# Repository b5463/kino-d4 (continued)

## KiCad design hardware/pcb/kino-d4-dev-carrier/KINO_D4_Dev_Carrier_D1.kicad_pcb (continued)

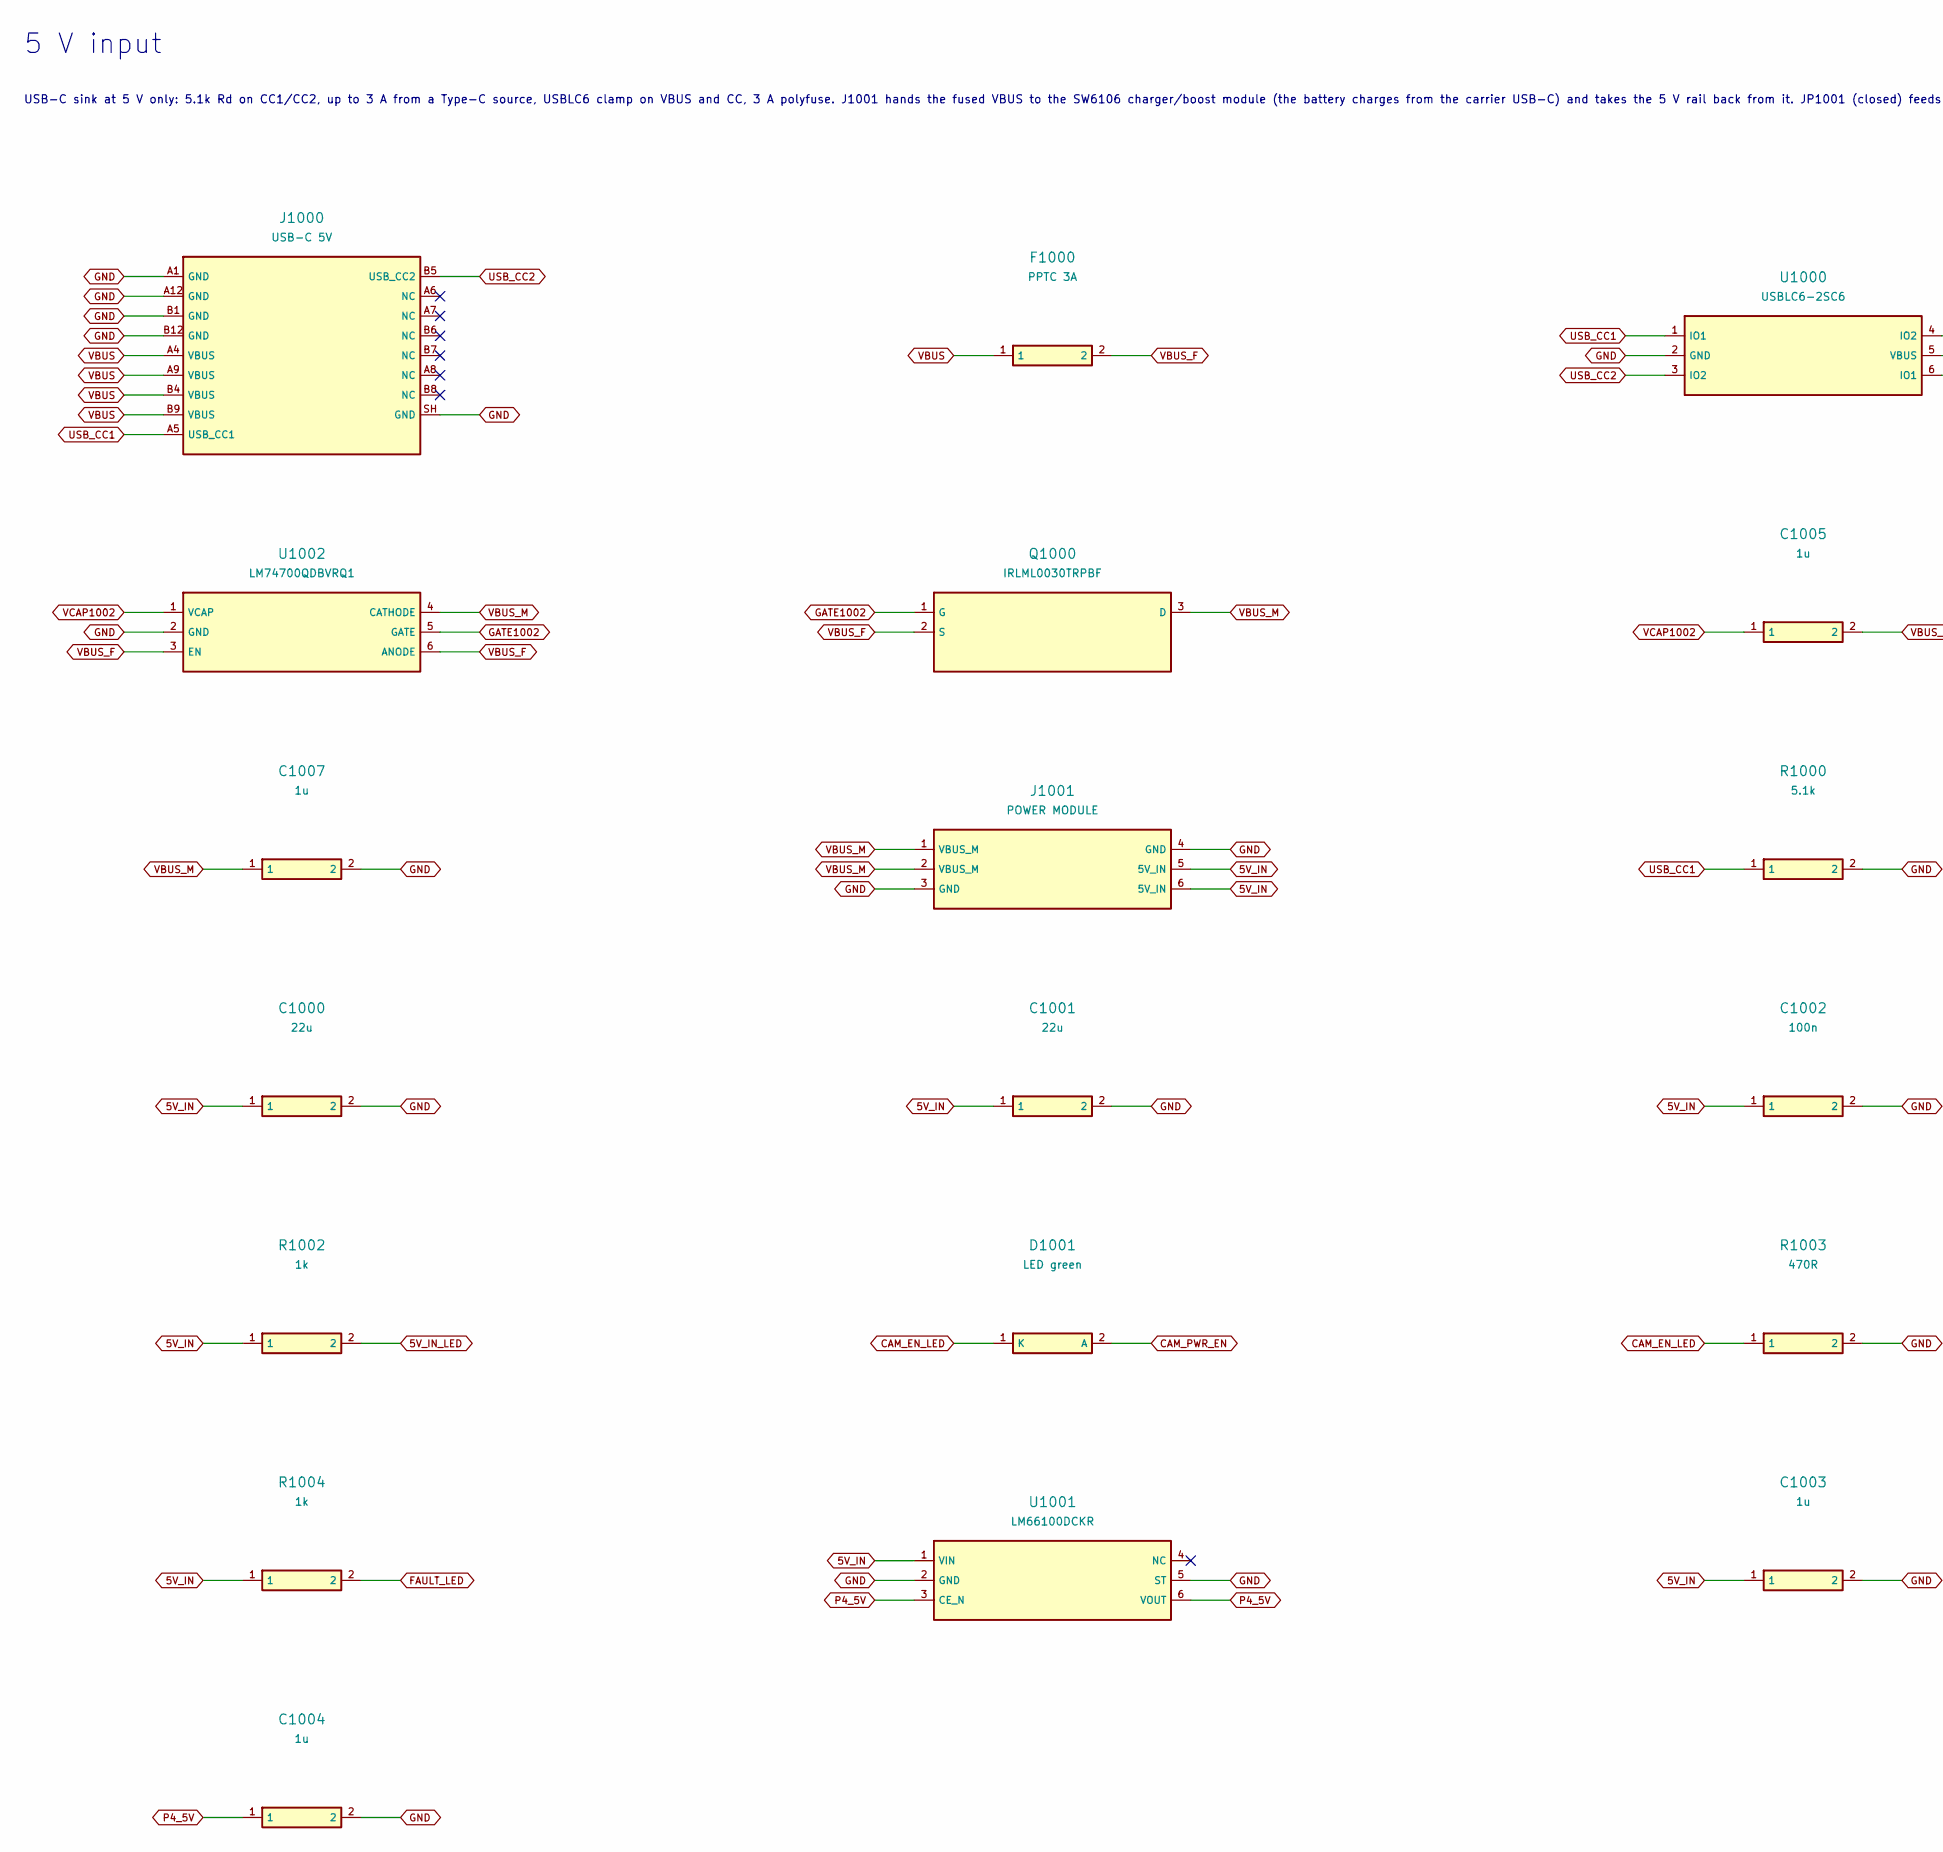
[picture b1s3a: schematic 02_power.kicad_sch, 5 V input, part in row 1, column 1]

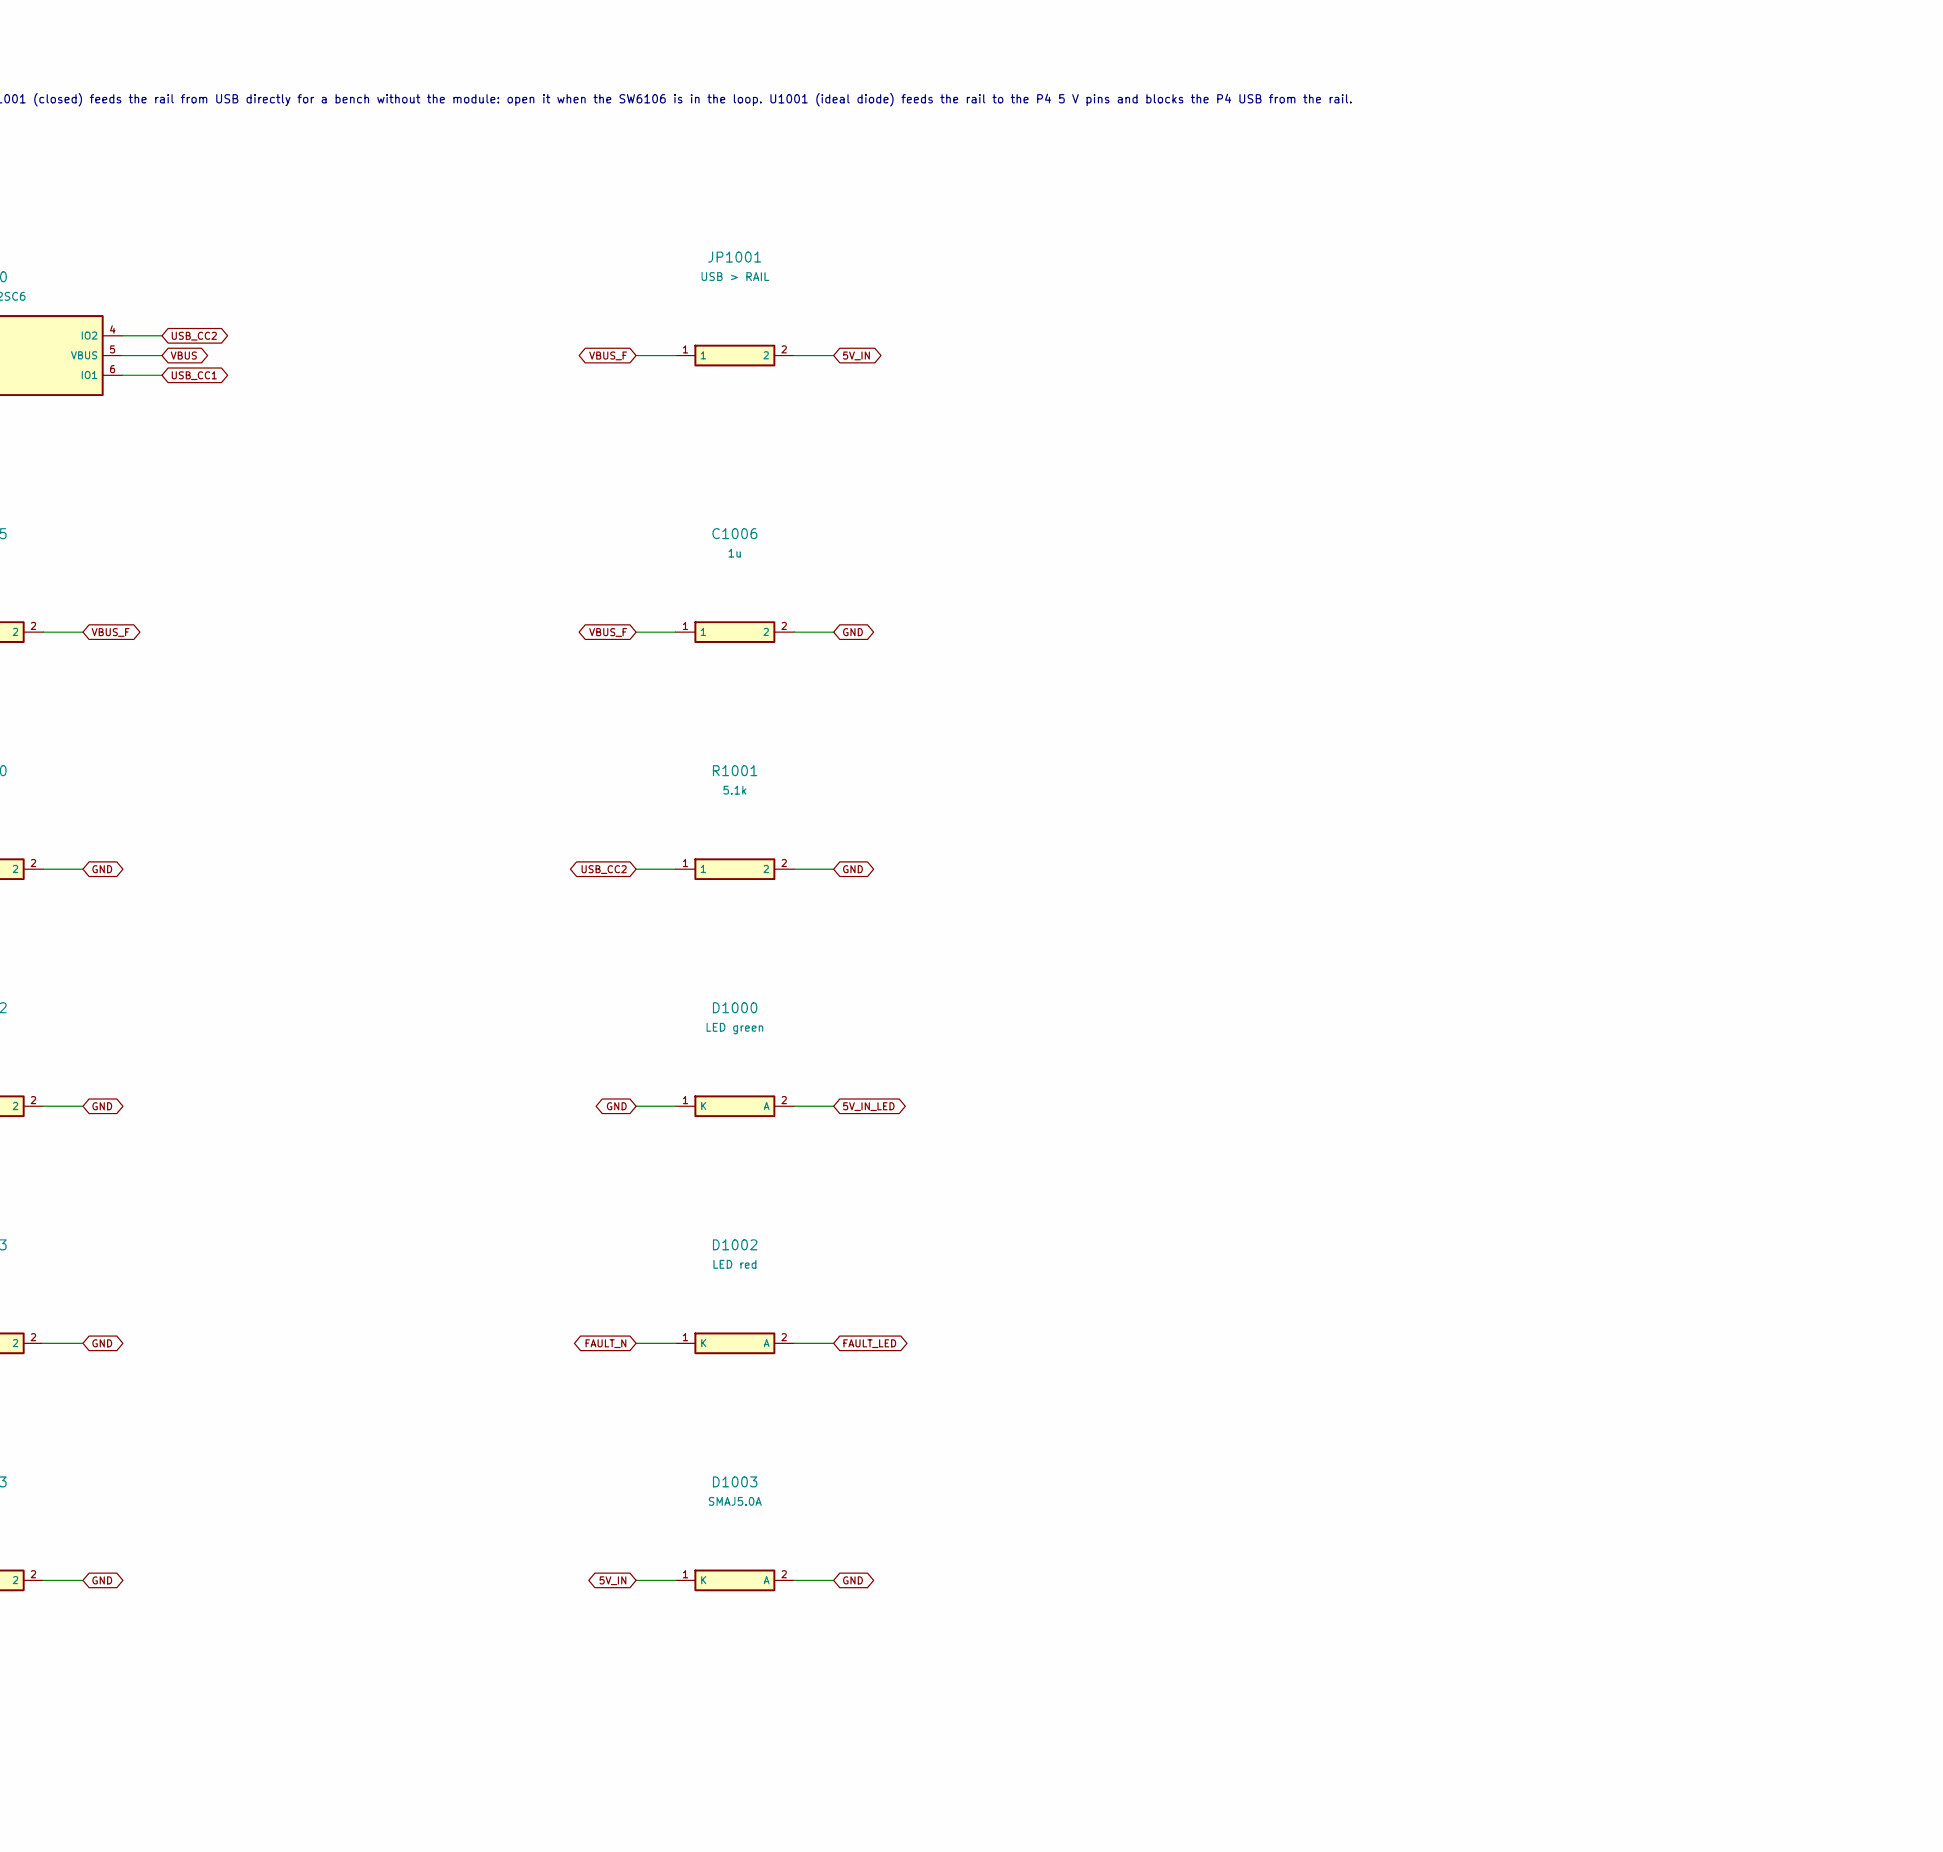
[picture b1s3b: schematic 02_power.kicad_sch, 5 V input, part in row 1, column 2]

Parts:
C1000, C1001: 22u; C_0805_2012Metric; LCSC C45783
C1002: 100n; C_0603_1608Metric; LCSC C14663
C1003, C1004, C1005, C1006, C1007: 1u; C_0603_1608Metric; LCSC C15849
D1000, D1001: LED green; LED_0805_2012Metric; LCSC C2297
D1002: LED red; LED_0603_1608Metric; LCSC C2286
D1003: SMAJ5.0A; D_SMA; LCSC C10758
F1000: PPTC 3A; Fuse_1812_4532Metric
J1000: USB-C 5V; USB_C_GCT_USB4105_KINO_GND0.05; LCSC C3020560
J1001: POWER MODULE; JST_XH_B6B-XH-A_1x06_P2.50mm_Vertical
JP1001: USB > RAIL; SolderJumper-2_P1.3mm_Bridged_RoundedPad1.0x1.5mm
Q1000: IRLML0030TRPBF; SOT-23; LCSC C67272
R1000, R1001: 5.1k; R_0603_1608Metric; LCSC C23186
R1002, R1004: 1k; R_0603_1608Metric; LCSC C21190
R1003: 470R; R_0603_1608Metric; LCSC C23179
U1000: USBLC6-2SC6; SOT-23-6; LCSC C7519
U1001: LM66100DCKR; SOT-363_SC-70-6; LCSC C2869734
U1002: LM74700QDBVRQ1; SOT-23-6; LCSC C2941042

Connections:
5V_IN: C1000.1, C1001.1, C1002.1, C1003.1, D1003.1 (K), J1001.5 (5V_IN), J1001.6 (5V_IN), JP1001.2, R1002.1, R1004.1, U1001.1 (VIN); also elsewhere on the board
5V_IN_LED: D1000.2 (A), R1002.2
CAM_EN_LED: D1001.1 (K), R1003.1
CAM_PWR_EN: D1001.2 (A); also elsewhere on the board
FAULT_LED: D1002.2 (A), R1004.2
FAULT_N: D1002.1 (K); also elsewhere on the board
GATE1002: Q1000.1 (G), U1002.5 (GATE)
GND: C1000.2, C1001.2, C1002.2, C1003.2, C1004.2, C1006.2, C1007.2, D1000.1 (K), D1003.2 (A), J1000.A1 (GND), J1000.A12 (GND), J1000.B1 (GND), J1000.B12 (GND), J1000.SH (GND), J1001.3 (GND), J1001.4 (GND), R1000.2, R1001.2, R1003.2, U1000.2 (GND), U1001.2 (GND), U1001.5 (ST), U1002.2 (GND); also elsewhere on the board
P4_5V: C1004.1, U1001.3 (CE_N), U1001.6 (VOUT); also elsewhere on the board
USB_CC1: J1000.A5 (USB_CC1), R1000.1, U1000.1 (IO1), U1000.6 (IO1)
USB_CC2: J1000.B5 (USB_CC2), R1001.1, U1000.3 (IO2), U1000.4 (IO2)
VBUS: F1000.1, J1000.A4 (VBUS), J1000.A9 (VBUS), J1000.B4 (VBUS), J1000.B9 (VBUS), U1000.5 (VBUS)
VBUS_F: C1005.2, C1006.1, F1000.2, JP1001.1, Q1000.2 (S), U1002.3 (EN), U1002.6 (ANODE)
VBUS_M: C1007.1, J1001.1 (VBUS_M), J1001.2 (VBUS_M), Q1000.3 (D), U1002.4 (CATHODE)
VCAP1002: C1005.1, U1002.1 (VCAP)

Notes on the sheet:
5 V input
USB-C sink at 5 V only: 5.1k Rd on CC1/CC2, up to 3 A from a Type-C source, USBLC6 clamp on VBUS and CC, 3 A polyfuse. J1001 hands the fused VBUS to the SW6106 charger/boost module (the battery charges from the carrier USB-C) and takes the 5 V rail back from it. JP1001 (closed) feeds the rail from 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

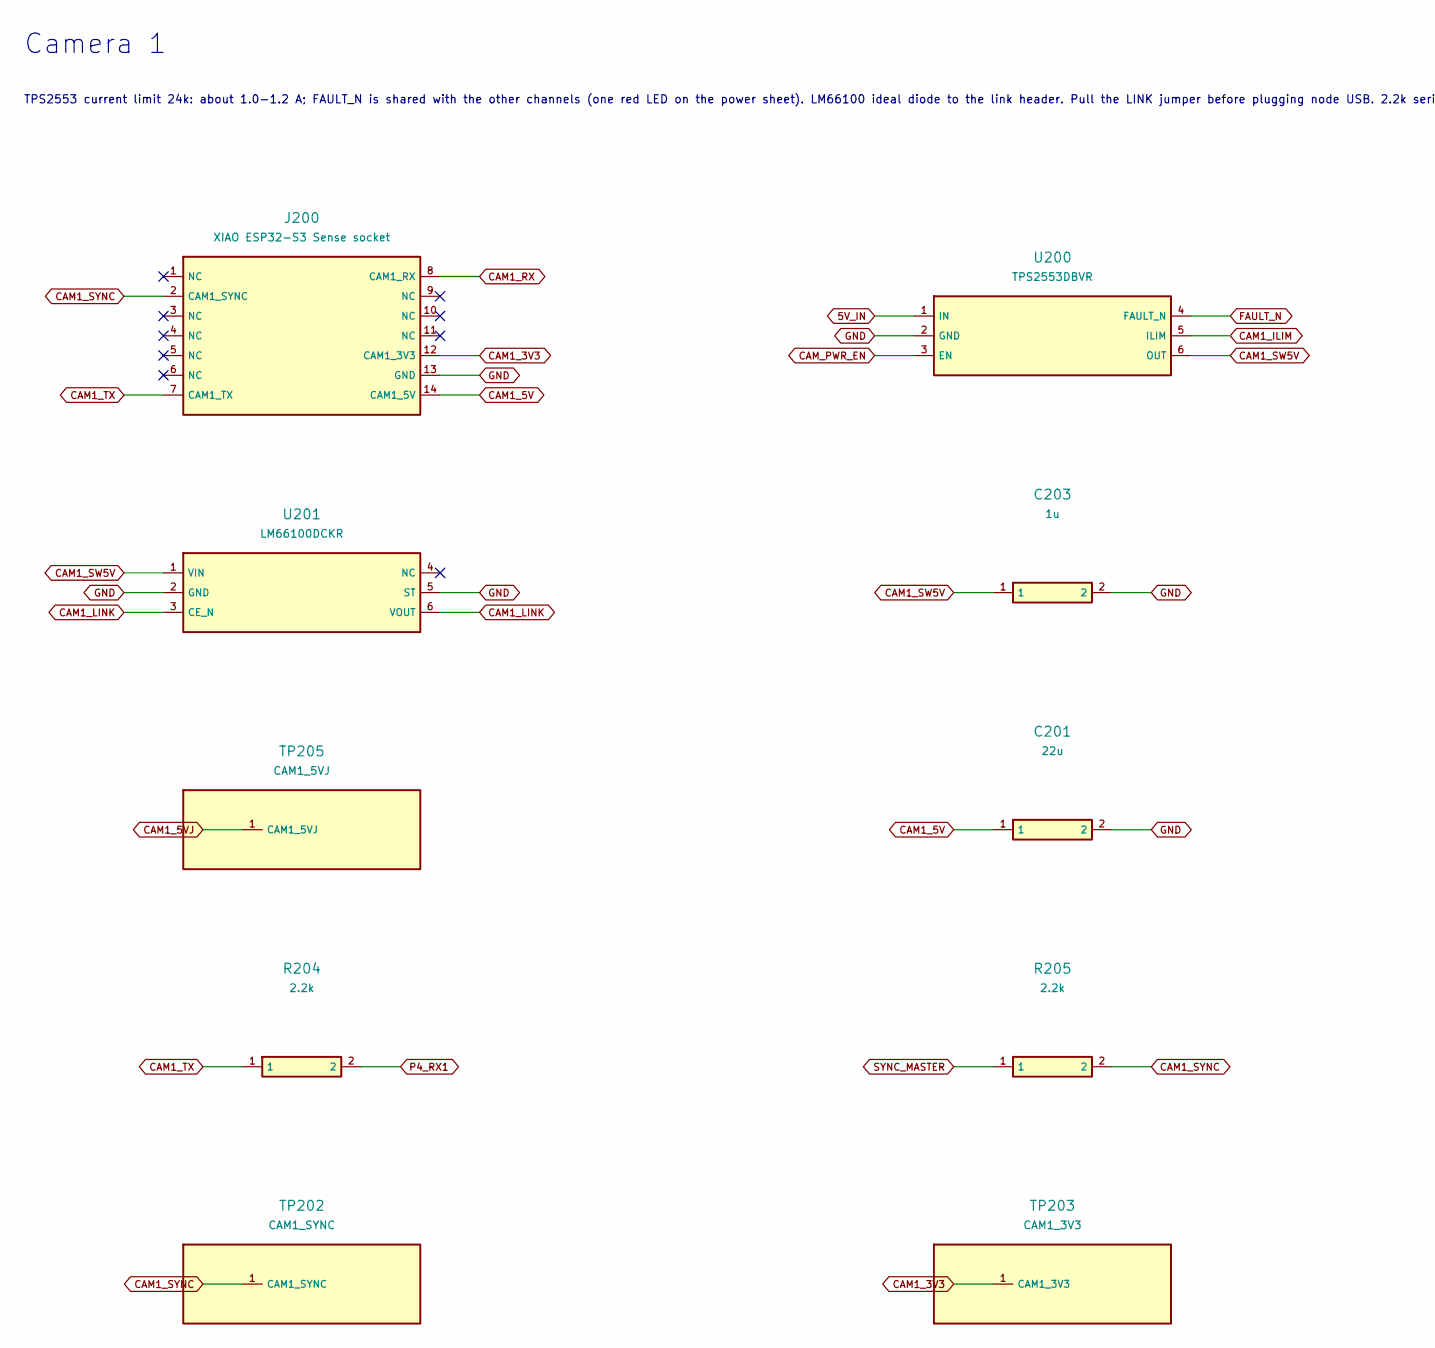
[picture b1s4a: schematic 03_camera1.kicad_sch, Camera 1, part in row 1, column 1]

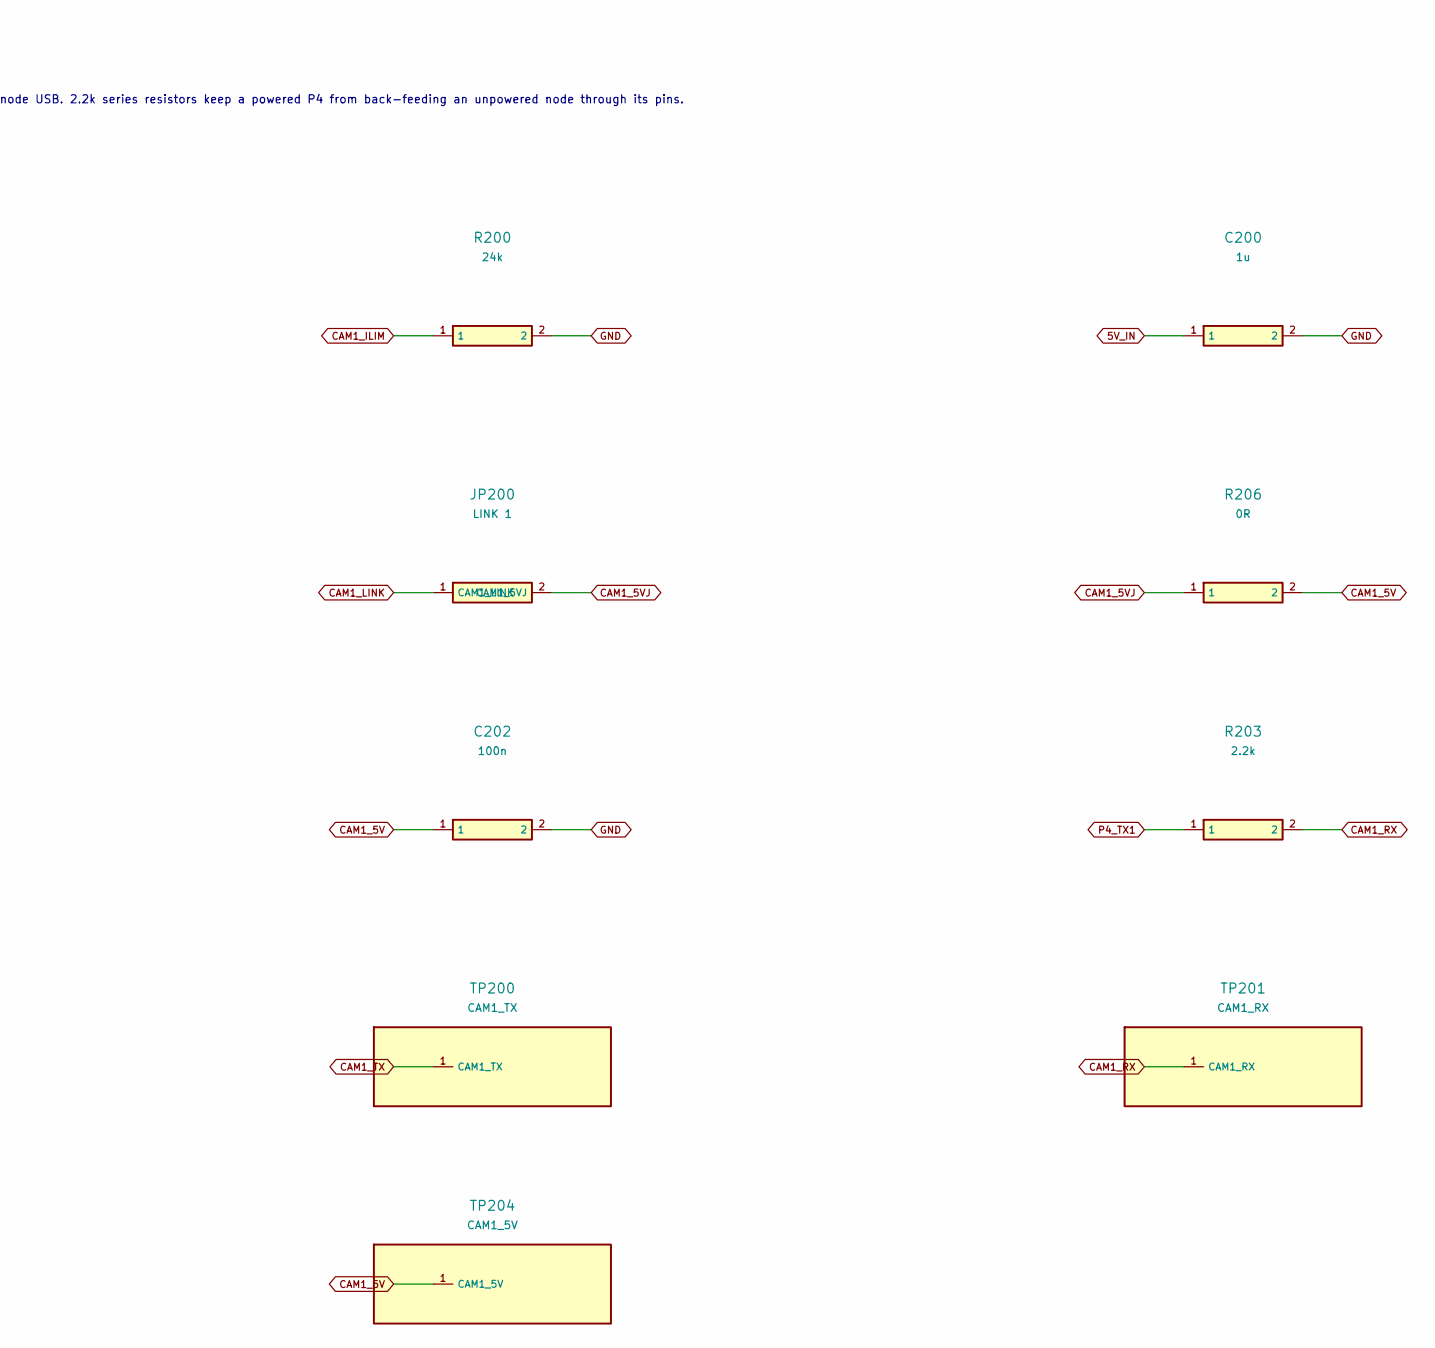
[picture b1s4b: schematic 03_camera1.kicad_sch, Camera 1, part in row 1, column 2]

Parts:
C200, C203: 1u; C_0603_1608Metric; LCSC C15849
C201: 22u; C_0805_2012Metric; LCSC C45783
C202: 100n; C_0603_1608Metric; LCSC C14663
J200: XIAO ESP32-S3 Sense socket; XIAO_Socket_15.24mm
JP200: LINK 1; PinHeader_1x02_P2.54mm_Vertical
R200: 24k; R_0603_1608Metric; LCSC C23352
R203, R204, R205: 2.2k; R_0603_1608Metric; LCSC C4190
R206: 0R; R_0603_1608Metric; LCSC C21189
TP200: CAM1_TX; TestPoint_Pad_D1.5mm
TP201: CAM1_RX; TestPoint_Pad_D1.5mm
TP202: CAM1_SYNC; TestPoint_Pad_D1.5mm
TP203: CAM1_3V3; TestPoint_Pad_D1.5mm
TP204: CAM1_5V; TestPoint_Pad_D1.5mm
TP205: CAM1_5VJ; TestPoint_Pad_D1.5mm
U200: TPS2553DBVR; SOT-23-6; LCSC C55266
U201: LM66100DCKR; SOT-363_SC-70-6; LCSC C2869734

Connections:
5V_IN: C200.1, U200.1 (IN); also elsewhere on the board
CAM1_3V3: J200.12 (CAM1_3V3), TP203.1
CAM1_5V: C201.1, C202.1, J200.14 (CAM1_5V), R206.2, TP204.1
CAM1_5VJ: JP200.2 (CAM1_5VJ), R206.1, TP205.1
CAM1_ILIM: R200.1, U200.5 (ILIM)
CAM1_LINK: JP200.1 (CAM1_LINK), U201.3 (CE_N), U201.6 (VOUT)
CAM1_RX: J200.8 (CAM1_RX), R203.2, TP201.1
CAM1_SW5V: C203.1, U200.6 (OUT), U201.1 (VIN)
CAM1_SYNC: J200.2 (CAM1_SYNC), R205.2, TP202.1
CAM1_TX: J200.7 (CAM1_TX), R204.1, TP200.1
CAM_PWR_EN: U200.3 (EN); also elsewhere on the board
FAULT_N: U200.4 (FAULT_N); also elsewhere on the board
GND: C200.2, C201.2, C202.2, C203.2, J200.13 (GND), R200.2, U200.2 (GND), U201.2 (GND), U201.5 (ST); also elsewhere on the board
P4_RX1: R204.2; also elsewhere on the board
P4_TX1: R203.1; also elsewhere on the board
SYNC_MASTER: R205.1; also elsewhere on the board

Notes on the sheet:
Camera 1
TPS2553 current limit 24k: about 1.0-1.2 A; FAULT_N is shared with the other channels (one red LED on the power sheet). LM66100 ideal diode to the link header. Pull the LINK jumper before plugging node USB. 2.2k series resistors keep a powered P4 from back-feeding an unpowered node through its pins.

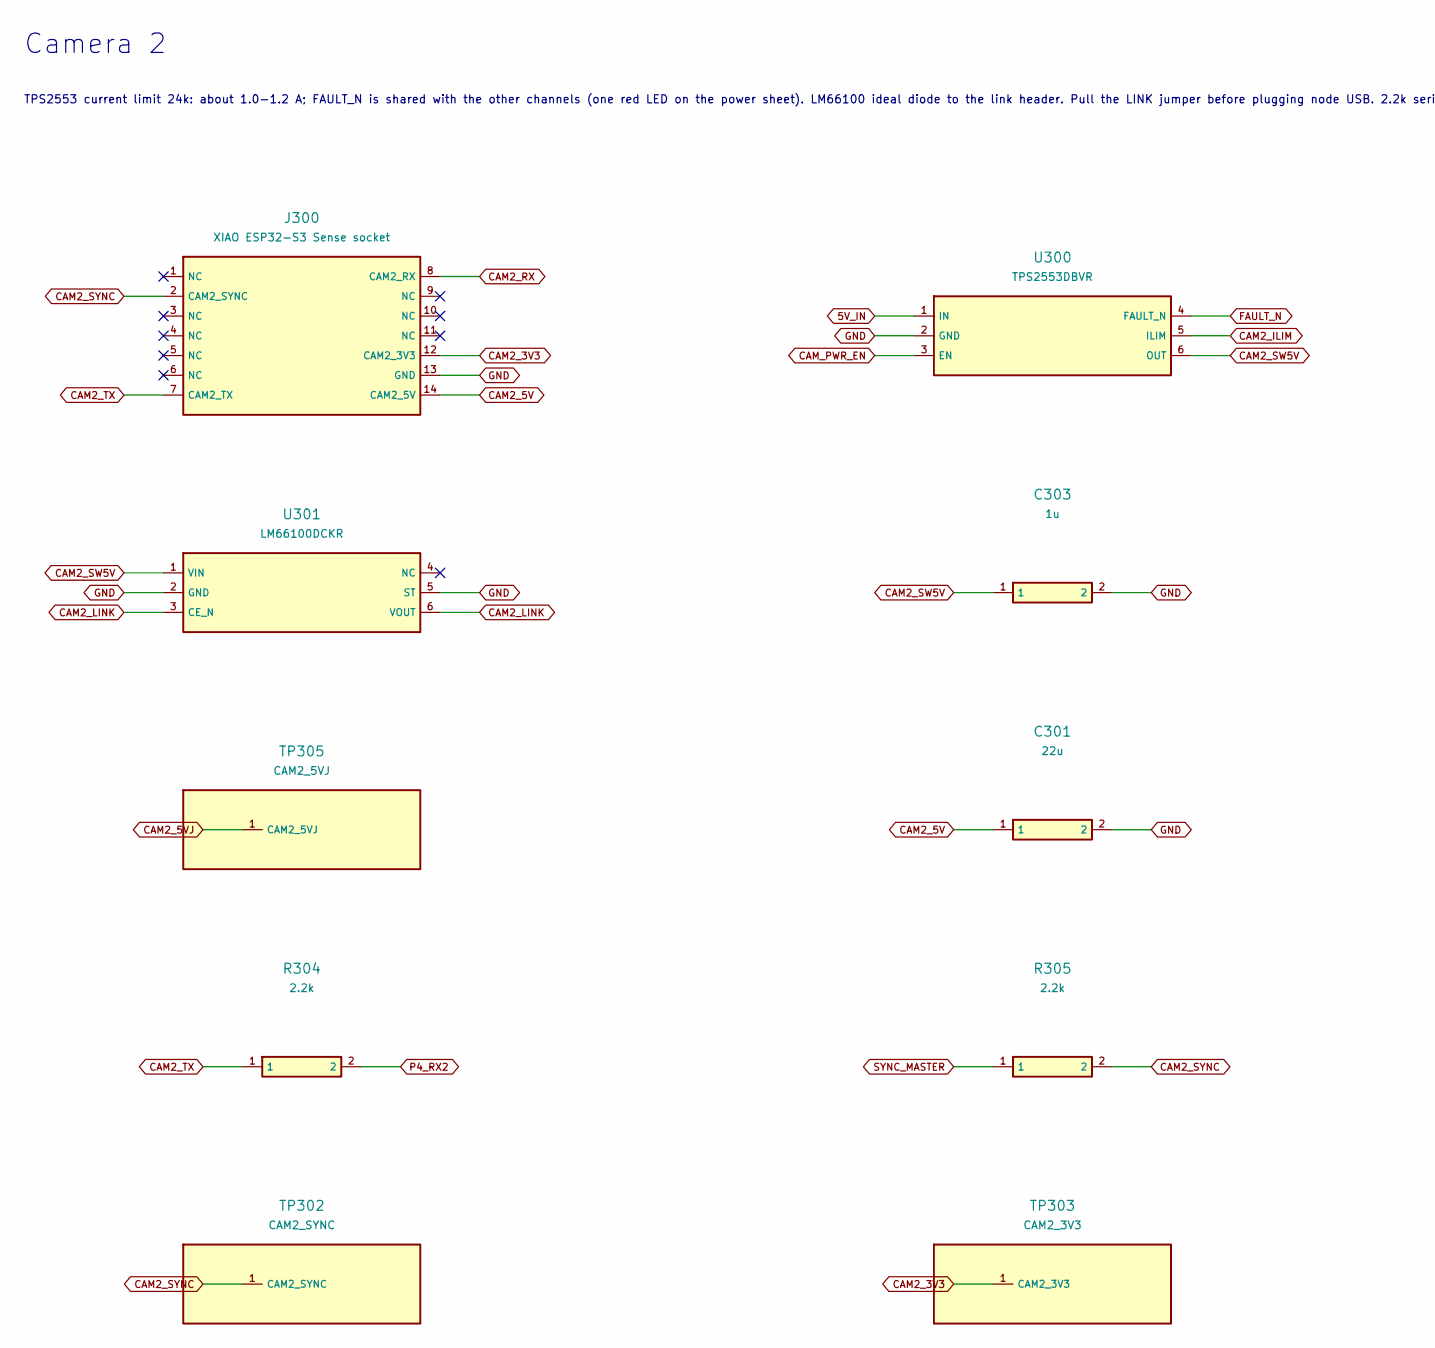
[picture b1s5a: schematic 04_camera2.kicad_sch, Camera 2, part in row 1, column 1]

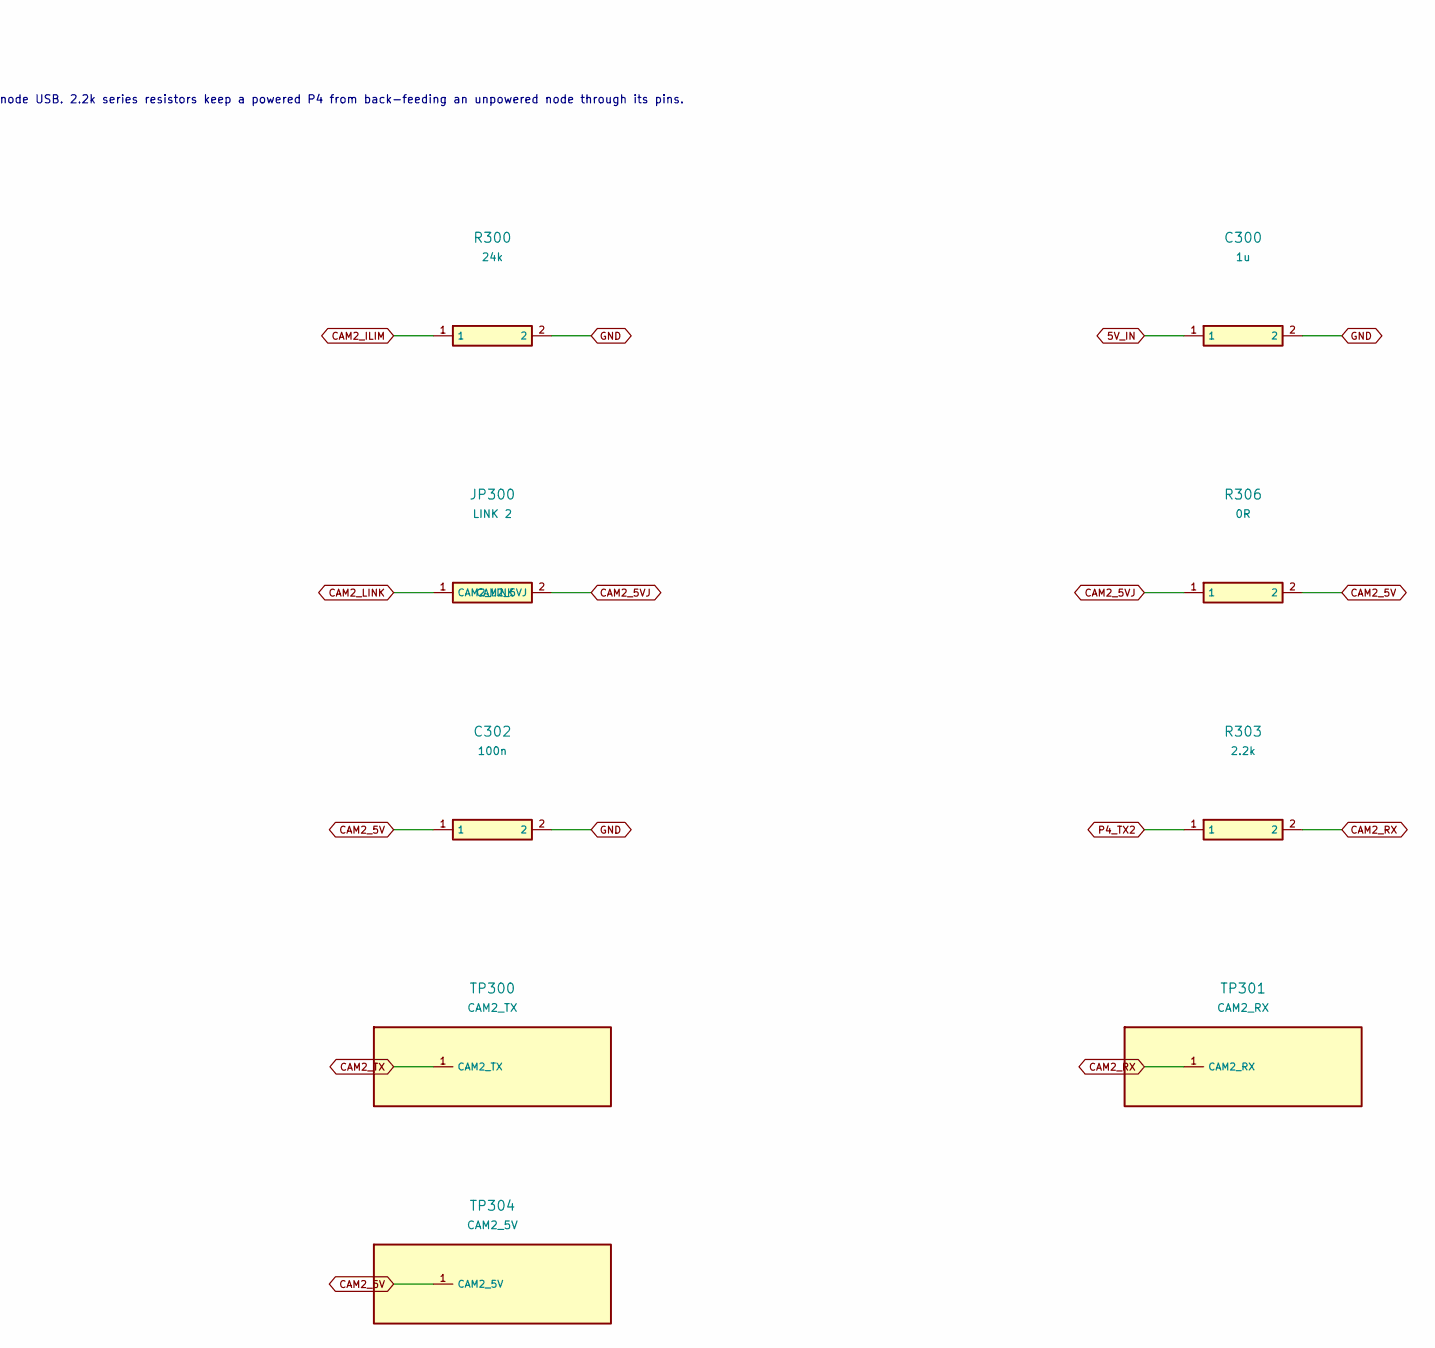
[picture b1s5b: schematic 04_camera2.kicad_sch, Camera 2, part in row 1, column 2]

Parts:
C300, C303: 1u; C_0603_1608Metric; LCSC C15849
C301: 22u; C_0805_2012Metric; LCSC C45783
C302: 100n; C_0603_1608Metric; LCSC C14663
J300: XIAO ESP32-S3 Sense socket; XIAO_Socket_15.24mm
JP300: LINK 2; PinHeader_1x02_P2.54mm_Vertical
R300: 24k; R_0603_1608Metric; LCSC C23352
R303, R304, R305: 2.2k; R_0603_1608Metric; LCSC C4190
R306: 0R; R_0603_1608Metric; LCSC C21189
TP300: CAM2_TX; TestPoint_Pad_D1.5mm
TP301: CAM2_RX; TestPoint_Pad_D1.5mm
TP302: CAM2_SYNC; TestPoint_Pad_D1.5mm
TP303: CAM2_3V3; TestPoint_Pad_D1.5mm
TP304: CAM2_5V; TestPoint_Pad_D1.5mm
TP305: CAM2_5VJ; TestPoint_Pad_D1.5mm
U300: TPS2553DBVR; SOT-23-6; LCSC C55266
U301: LM66100DCKR; SOT-363_SC-70-6; LCSC C2869734

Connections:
5V_IN: C300.1, U300.1 (IN); also elsewhere on the board
CAM2_3V3: J300.12 (CAM2_3V3), TP303.1
CAM2_5V: C301.1, C302.1, J300.14 (CAM2_5V), R306.2, TP304.1
CAM2_5VJ: JP300.2 (CAM2_5VJ), R306.1, TP305.1
CAM2_ILIM: R300.1, U300.5 (ILIM)
CAM2_LINK: JP300.1 (CAM2_LINK), U301.3 (CE_N), U301.6 (VOUT)
CAM2_RX: J300.8 (CAM2_RX), R303.2, TP301.1
CAM2_SW5V: C303.1, U300.6 (OUT), U301.1 (VIN)
CAM2_SYNC: J300.2 (CAM2_SYNC), R305.2, TP302.1
CAM2_TX: J300.7 (CAM2_TX), R304.1, TP300.1
CAM_PWR_EN: U300.3 (EN); also elsewhere on the board
FAULT_N: U300.4 (FAULT_N); also elsewhere on the board
GND: C300.2, C301.2, C302.2, C303.2, J300.13 (GND), R300.2, U300.2 (GND), U301.2 (GND), U301.5 (ST); also elsewhere on the board
P4_RX2: R304.2; also elsewhere on the board
P4_TX2: R303.1; also elsewhere on the board
SYNC_MASTER: R305.1; also elsewhere on the board

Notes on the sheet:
Camera 2
TPS2553 current limit 24k: about 1.0-1.2 A; FAULT_N is shared with the other channels (one red LED on the power sheet). LM66100 ideal diode to the link header. Pull the LINK jumper before plugging node USB. 2.2k series resistors keep a powered P4 from back-feeding an unpowered node through its pins.
